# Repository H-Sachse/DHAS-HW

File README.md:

# DHAS-HW
Hardware related information for Distributed Homeautomation System

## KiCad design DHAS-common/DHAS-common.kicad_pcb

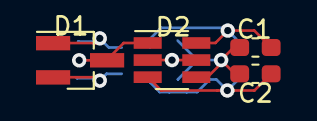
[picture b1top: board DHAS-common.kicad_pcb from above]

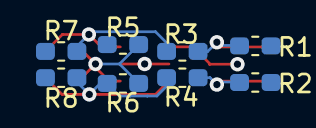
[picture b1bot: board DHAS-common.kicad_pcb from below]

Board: 2 copper layers, 12 parts (8 on the bottom side), 6 nets.

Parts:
C1, C2: 47nF; C_0603_1608Metric_Pad1.05x0.95mm_HandSolder
D1: MMBZ12V; SOT-23_Handsoldering
D2: D_Schottky_double_x2_Serial_A1K1C2A2K2C1; SOT-23-6_Handsoldering
R1, R2: 100R; R_0603_1608Metric_Pad1.05x0.95mm_HandSolder
R3, R4: 10k; R_0603_1608Metric_Pad1.05x0.95mm_HandSolder
R5, R6: 3.9k; R_0603_1608Metric_Pad1.05x0.95mm_HandSolder
R7, R8: 1k; R_0603_1608Metric_Pad1.05x0.95mm_HandSolder

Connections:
/DSI1/VIO: D2.2, D2.5
GND: C1.2, C2.2, D1.3, D2.1, D2.4, R5.2, R6.2
unnamed: C1.1, D2.6, R3.1, R5.1, R7.2
unnamed: C2.1, D2.3, R4.1, R6.1, R8.2
unnamed: D1.1, R1.2, R3.2
unnamed: D1.2, R2.2, R4.2

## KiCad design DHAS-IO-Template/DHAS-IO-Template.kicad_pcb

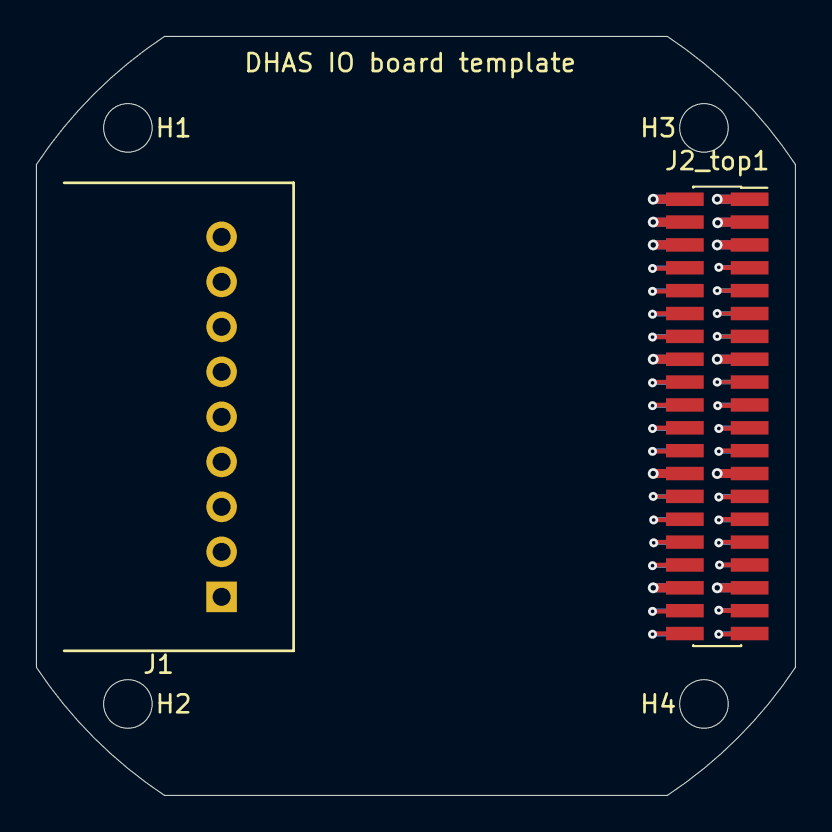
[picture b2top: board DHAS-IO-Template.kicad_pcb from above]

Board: 4 copper layers, 42.2 x 42.2 mm, 7 parts (1 on the bottom side), 32 nets.

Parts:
H1, H2, H3, H4: MountingHole; MountingHole_2.7mm_M2.5
J1: Conn_01x09_Male; TE_EP2.5_9p_Horizontal
J2_bot1: Conn_02x20_Odd_Even; PinHeader_2x20_P1.27mm_Vertical_SMD
J2_top1: Conn_02x20_Odd_Even; PinSocket_2x20_P1.27mm_Vertical_SMD

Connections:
+3V3: J2_bot1.4, J2_top1.4
+5V: J2_bot1.3, J2_top1.3
/J2-32: J2_bot1.32, J2_top1.32
/PIO0_0: J2_bot1.7, J2_top1.7
/PIO0_1: J2_bot1.8, J2_top1.8
/PIO0_2: J2_bot1.9, J2_top1.9
/PIO0_3: J2_bot1.10, J2_top1.10
/PIO0_4: J2_bot1.11, J2_top1.11
/PIO0_5: J2_bot1.12, J2_top1.12
/PIO0_6: J2_bot1.13, J2_top1.13
/PIO0_7: J2_bot1.14, J2_top1.14
/PIO0_8: J2_bot1.17, J2_top1.17
/PIO0_9: J2_bot1.18, J2_top1.18
/PIO0_10: J2_bot1.19, J2_top1.19
/PIO0_11: J2_bot1.20, J2_top1.20
/PIO1_0: J2_bot1.21, J2_top1.21
/PIO1_1: J2_bot1.22, J2_top1.22
/PIO1_2: J2_bot1.23, J2_top1.23
/PIO1_3: J2_bot1.24, J2_top1.24
/PIO1_4: J2_bot1.27, J2_top1.27
/PIO1_5: J2_bot1.28, J2_top1.28
/PIO1_6: J2_bot1.29, J2_top1.29
/PIO1_7: J2_bot1.30, J2_top1.30
/PIO1_8: J2_bot1.31, J2_top1.31
/PIO1_10: J2_bot1.33, J2_top1.33
/PIO1_11: J2_bot1.34, J2_top1.34
/PIO2_0: J2_bot1.37, J2_top1.37
/PIO2_1: J2_bot1.38, J2_top1.38
/PIO2_2: J2_bot1.39, J2_top1.39
/PIO2_3: J2_bot1.40, J2_top1.40
/V12P: J2_bot1.1, J2_bot1.2, J2_top1.1, J2_top1.2
GND: J2_bot1.5, J2_bot1.6, J2_bot1.15, J2_bot1.16, J2_bot1.25, J2_bot1.26, J2_bot1.35, J2_bot1.36, J2_top1.5, J2_top1.6, J2_top1.15, J2_top1.16, J2_top1.25, J2_top1.26, J2_top1.35, J2_top1.36

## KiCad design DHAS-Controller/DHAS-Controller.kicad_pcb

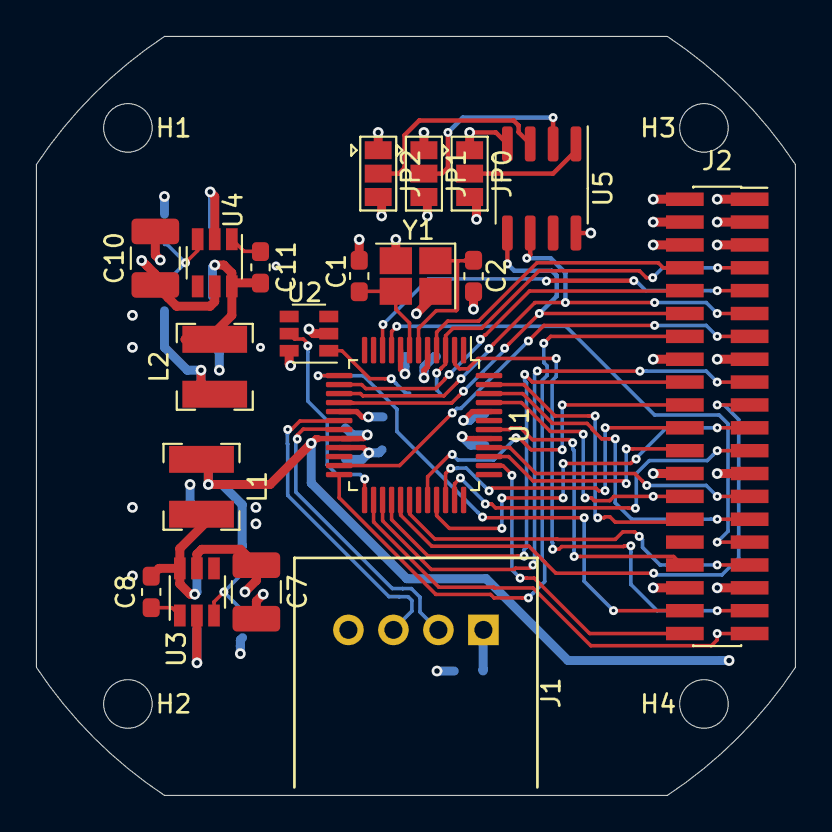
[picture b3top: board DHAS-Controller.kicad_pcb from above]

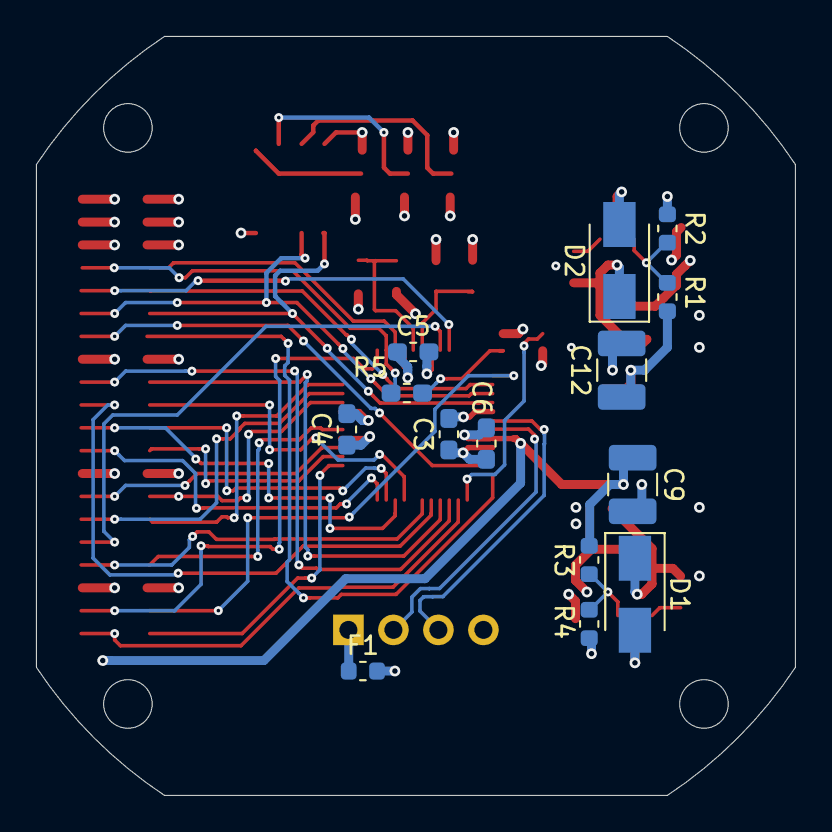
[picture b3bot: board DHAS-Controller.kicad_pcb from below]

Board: 4 copper layers, 42.2 x 42.2 mm, 37 parts (14 on the bottom side), 47 nets.

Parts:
C1, C2: 39pF; C_0603_1608Metric_Pad1.05x0.95mm_HandSolder
C3, C4, C5, C6: 47nF; C_0603_1608Metric_Pad1.05x0.95mm_HandSolder
C7, C9, C10, C12: 22uF; C_1210_3225Metric_Pad1.42x2.65mm_HandSolder
C8, C11: 10nF; C_0603_1608Metric_Pad1.05x0.95mm_HandSolder
D1, D2: D; D_SMA
F1: Fuse_Small; Fuse_0603_1608Metric
H1, H2, H3, H4: MountingHole; MountingHole_2.7mm_M2.5
J1: Conn_01x04_Male; TE_EP2.5_4p_Horizontal
J2: Conn_02x20_Odd_Even; PinSocket_2x20_P1.27mm_Vertical_SMD
JP0, JP1, JP2: SolderJumper_3_Open; SolderJumper-3_P1.3mm_Open_Pad1.0x1.5mm
L1, L2: 68uH; L_Bourns-SRN4018
R1, R3: 49.9k; R_0603_1608Metric
R2: 16.2k; R_0603_1608Metric
R4: 10k; R_0603_1608Metric
R5: 1k; R_0603_1608Metric_Pad1.05x0.95mm_HandSolder
U1: LPC11C24; LQFP-48_7x7mm_P0.5mm
U2: APX825A-26; SOT-23-6
U3, U4: AP3211; TSOT-23-6
U5: M24C64-RMN; SOIC-8_3.9x4.9mm_P1.27mm
Y1: 12MHz; Crystal_SMD_EuroQuartz_X22-4Pin_2.5x2.0mm_HandSoldering

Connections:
+3V3: C3.2, C4.2, C5.2, C12.1, J2.4, JP0.3, JP1.3, JP2.3, L2.2, R1.1, U1.8, U1.17, U1.44, U2.6, U5.8
+5V: C6.2, C9.1, J2.3, L1.2, R3.1, U1.20
/CAN_N: J1.3, U1.18
/CAN_P: J1.2, U1.19
/EEP_A0: JP0.2, U5.1
/EEP_A1: JP1.2, U5.2
/EEP_A2: JP2.2, U5.3
/MCU/PIO2_10: U1.25, U2.5
/PIO0_0: J2.7, R5.1, U1.3
/PIO0_1: J2.8, U1.4
/PIO0_2: J2.9, U1.10
/PIO0_3: J2.10, U1.14
/PIO0_4: J2.11, U1.15, U5.6
/PIO0_5: J2.12, U1.16, U5.5
/PIO0_6: J2.13, U1.23
/PIO0_7: J2.14, U1.24
/PIO0_8: J2.17, U1.27
/PIO0_9: J2.18, U1.28
/PIO0_10: J2.19, U1.29
/PIO0_11: J2.20, U1.32
/PIO1_0: J2.21, U1.33
/PIO1_1: J2.22, U1.34
/PIO1_2: J2.23, U1.35
/PIO1_3: J2.24, U1.39
/PIO1_4: J2.27, U1.40
/PIO1_5: J2.28, U1.45
/PIO1_6: J2.29, U1.46
/PIO1_7: J2.30, U1.47
/PIO1_8: J2.31, U1.9
/PIO1_10: J2.33, U1.30
/PIO1_11: J2.34, U1.42
/PIO2_0: J2.37, U1.2
/PIO2_1: J2.38, U1.13
/PIO2_2: J2.39, U1.26
/PIO2_3: J2.40, U1.38
/PSU_V3P3/BS: C11.1, U4.1
/PSU_V3P3/FB: R1.2, R2.1, U4.3
/PSU_V3P3/SW: C11.2, D2.1, L2.1, U4.6
/PSU_V5P/BS: C8.1, U3.1
/PSU_V5P/FB: R3.2, R4.1, U3.3
/PSU_V5P/SW: C8.2, D1.1, L1.1, U3.6
/V12P: C7.1, C10.1, F1.2, J2.1, J2.2, U3.5, U4.5
GND: C1.1, C2.1, C3.1, C4.1, C5.1, C6.1, C7.2, C9.2, C10.2, C12.2, D1.2, D2.2, J1.4, J2.5, J2.6, J2.15, J2.16, J2.25, J2.26, J2.35, J2.36, JP0.1, JP1.1, JP2.1, R2.2, R4.2, U1.5, U1.21, U1.41, U2.2, U3.2, U4.2, U5.4, Y1.2, Y1.4
unnamed: C1.2, U1.7, Y1.3
unnamed: C2.2, U1.6, Y1.1
unnamed: F1.1, J1.1
unnamed: R5.2, U2.1

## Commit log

2020-06-24 initial commit of DHAS component and footprint libraries
2020-06-24 initial commit of DHAS Controller board schematics and layout
2020-06-24 add missing mounting hole in connector footprint
2020-06-24 update template with fixed connector footprint
2020-06-24 add licence and readme
2020-07-14 add missing subdesign schematics to DHAS-Controller
2020-07-14 add missing lib tables
2020-08-13 move DHAS-IO-Template into "root" folder to make relative library paths work fix connector placement in layout fix footprint path
2020-08-13 add project with common subdesign "DSI_VCC_2x"
